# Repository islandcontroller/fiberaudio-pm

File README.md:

# fiberaudio-pm 

A *Pmod&trade; Compatible* peripheral module featuring a pair of active optical audio transmitter/receivers.

<p align="center">
  
</picture></p>

View [**Schematic**](doc/fiberaudio-pm.pdf) &#128196; or [**PCB Preview**](https://htmlpreview.github.io/?https://github.com/islandcontroller/fiberaudio-pm/blob/master/doc/ibom.html) &#127760;.

### Key features

* One pair of active optical audio transmitter/receiver modules (JIS F05, e.g. TOSLINK&trade;)
* One *Digilent Pmod&trade; Compatible* 1x6 pin header
    * Interface Type 1 (GPIO)
* Fully compliant with the [*Digilent Pmod&trade; Interface Specification*, Version 1.3.1](https://digilent.com/reference/_media/reference/pmod/pmod-interface-specification-1_3_1.pdf)

## Overview

The *Pmod&trade; Compatible* fiberaudio-pm peripheral module features a pair of active optical audio transmitter/receiver modules, commonly referred to as "optical S/PDIF". The module allows embedded developers to explore optical data transfer technologies using *Digilent Pmod&trade;* ecosystem components, such as FPGA development boards.

## Review Notes (`Rev.2`)

* CE marking requires compliance with [Directive 2015/863 (EU) amending Annex II to Directive 2011/65/EU](https://eur-lex.europa.eu/legal-content/EN/TXT/?uri=CELEX:32015L0863) (RoHS)
* WEEE marking not required if the board is classified as a 'component' according to [FAQ on Directive 2012/19/EU](https://ec.europa.eu/environment/pdf/waste/weee/faq.pdf) (WEEE)
  * Removed marking in `Rev.3`
* Heat-sinking effect of GND pad thermal spokes is excessive at 400µm width
  * Adjusted to 250µm in `Rev.4`
* "VCC" and "GND" silkscreen placed too close to connector `J1`. Stroke could be a bit wider for better readability.
  * Adjusted position and size in `Rev.4`

## Resources

* [Digilent Pmod&trade; License Agreement](https://digilent.com/reference/_media/pmod/pmod/pmod_license_agreement.pdf)
* Digilent Reference: [Programmable Logic](https://digilent.com/reference/programmable-logic/start)

## Licensing

If not stated otherwise within the specific file, the contents of this project are licensed under the CERN Open Hardware Licence Version 2 - Permissive. The full license text is provided in the [`LICENSE`](LICENSE) document.

    SPDX-License-Identifier: CERN-OHL-P-2.0

This licensing model is compliant with the [Open Source Hardware Definition 1.0](https://www.oshwa.org/definition/).

## Legal Notice

"Digilent" is a registered trademark of *Digilent, Inc*. All other trademarks and registered trademarks mentioned herein are property of their respective owners.

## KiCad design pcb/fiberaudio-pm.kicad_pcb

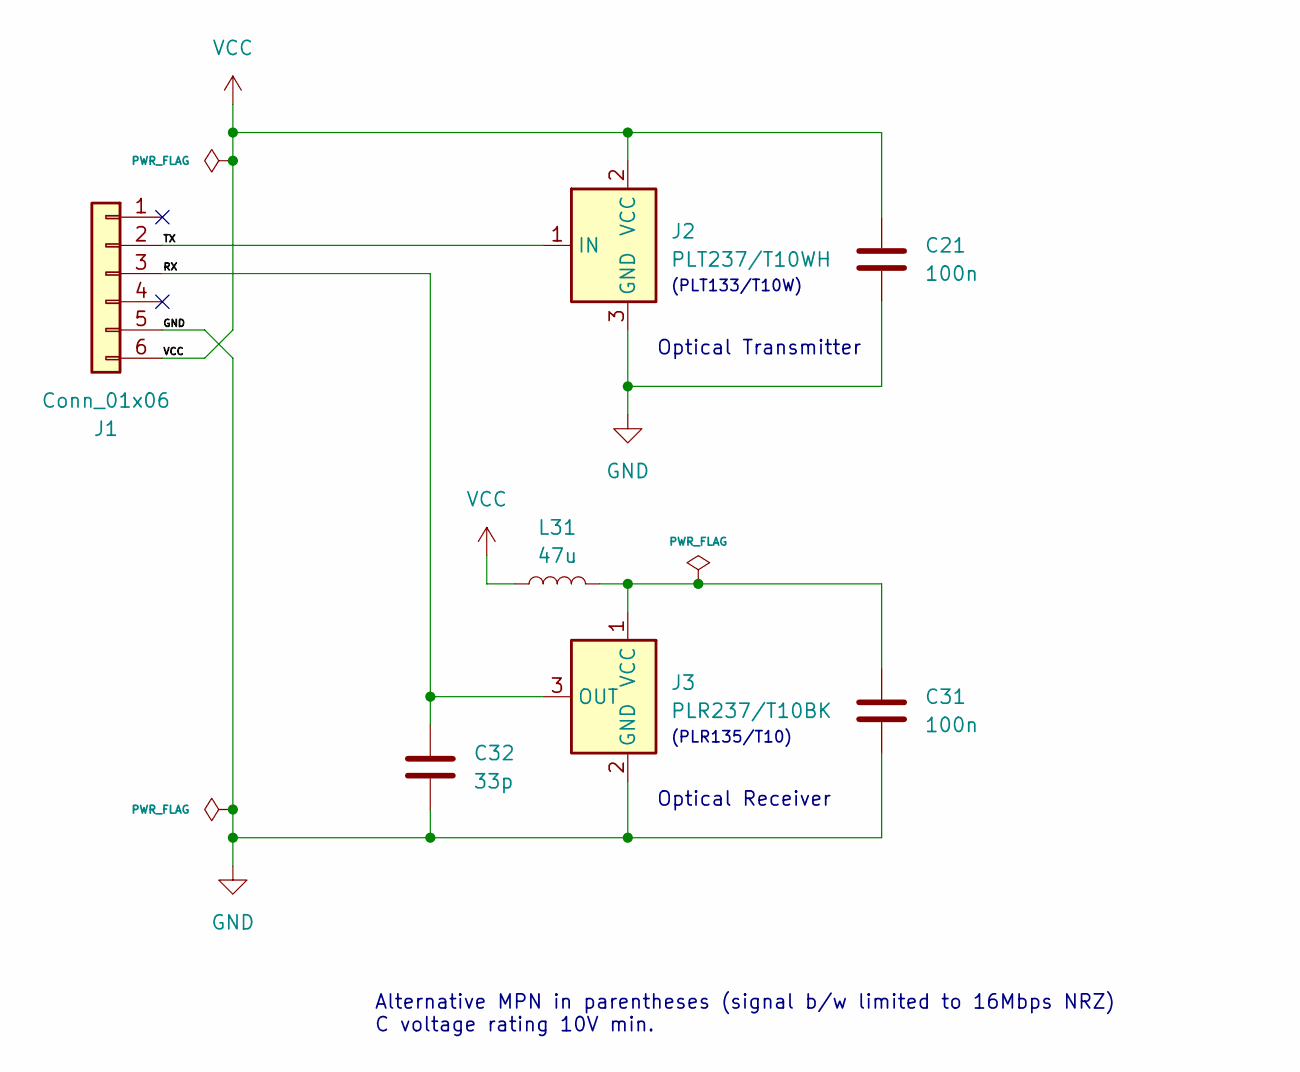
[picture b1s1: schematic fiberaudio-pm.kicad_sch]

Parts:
C21, C31: 100n; C_0805_2012Metric
C32: 33p; C_0805_2012Metric
J1: Conn_01x06; PinHeader_1x06_P2.54mm_Horizontal_Mirrored
J2: PLT237/T10WH; Connector_T10
J3: PLR237/T10BK; Connector_T10
L31: 47u; L_0805_2012Metric

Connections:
/RX: C32.1, J1.3, J3.3 (OUT)
/TX: J1.2, J2.1 (IN)
GND: C21.2, C31.2, C32.2, J1.5, J2.3 (GND), J3.2 (GND)
unnamed: C31.1, J3.1 (VCC), L31.2
VCC: C21.1, J1.6, J2.2 (VCC), L31.1

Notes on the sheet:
Optical Transmitter
Optical Receiver
Alternative MPN in parentheses (signal b/w limited to 16Mbps NRZ) C voltage rating 10V min.
(PLR135/T10)
(PLT133/T10W)

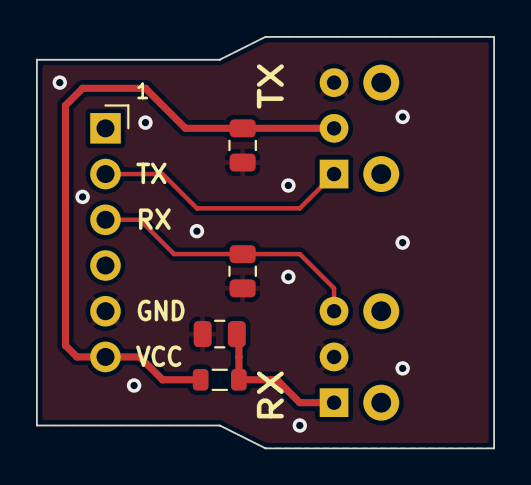
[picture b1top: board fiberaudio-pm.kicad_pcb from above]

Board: 2 copper layers, 25.4 x 22.9 mm, 7 parts (0 on the bottom side), 5 nets.

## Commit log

2024-01-22 Added rev.1 schematic and layout; Added license and pcb mfg badges; Updated preview image
2024-01-22 Fixed pin-swap on J3; Updated to Rev.2; Updated documentation
2024-01-25 Re-classified as 'component' acc. to FAQ on Directive 2012/19/EU (WEEE2), see http://ec.europa.eu/environment/waste/weee/pdf/faq.pdf; Removed WEEE logo; Added note regarding RoHS compliance requireme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
2024-01-26 Reduced thermal spoke width to 0.25um; Adjusted layout; Adjusted text placement and size
2024-01-26 Updated board preview renderings
2024-01-26 Added review notes for PCB Rev.2

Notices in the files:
README.md:
license - CERN-OHL-P-2.0
